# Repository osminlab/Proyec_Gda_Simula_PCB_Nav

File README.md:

<!-- Para mejorar la estructura de mi README.md hice uso de la siguiente web y criterios personales:
    	                https://www.makeareadme.com/
 -->

# **Proyecto de Graduación:** "Simulación de trayectoria de un globo sonda para dimensionamiento de subsistema de navegación para misiones a la estratosfera" 🎈

**ESTADO: Finalizado Junio/2023 (CERRADO).**

El presente es una simulación de trayectoria ascendete y descendete de un globo-sonda hasta los 30 Km en el cual se  analizaron diferentes parámetros que se consideron clave a lo largo de su recorrido, se elaboró un análisis exploratorio (EDA) en los datos generados en la simulación  que finalizó con una propuesta de dimensionamiento a subsistema de navegación Low-cost, desarrollando su respectivo esquemático del circuito y layout de la PCB para una posible fabricación.  

Este es un proyecto de graduación, realizado en la [Universidad Don Bosco (UDB)](https://www.udb.edu.sv/udb/) por Osmin Larreynaga con asesoria de Msc. Napoleón Cornejo. Este microproyecto (trabajo de graduación) forma parte del macroproyecto "Diseño de una misión  globo de gran altitud - StratoBallon" realizado con una dependencia de la universidad llamada [Observatorio Micro Macro (OMM)](http://omm.udb.edu.sv/omm/public/) 

## Indice: 
- [Generalidades del Trabajo](#Generalidades-trabajo)
- [Estructura del repositorio (sub-carpetas)](#estructura-del-repositorio--sub-carpetas)
  * [Carpeta code](#estructura-del-repositorio--sub-carpetas)
  * [Carpeta document](#estructura-del-repositorio--sub-carpetas)
  * [Carpeta hardware](#estructura-del-repositorio--sub-carpetas)
- [Puntos destacados](#puntos-destacados)
- [Licencia](#licencia)

<h2> 
    
    Generalidaddes del Trabajo ⚙️💡
</h2>  

Este repositorio incluye  como producto final lo siguiente:

* **Simulación:** Código fuente escrito en Python de la "Simulacion de trayectoria del Globo de Gran Altitud" haciendo usos de Jupyter Notebooks. [Ver código](https://github.com/osminlab/Proyec_Gda_Simula_PCB_Nav/tree/main/code) o revisar en la sigiente ruta `./code/src`.
* **Documento:**  Escrito final del proyecto de graduación desarrollado en $\LaTeX$, se registra académicamente en detalle y de forma formal en que consiste el presente trabajo. Puede ver el documento en PDF si desconoce sobre $\LaTeX$ click [aquí](https://github.com/osminlab/Proyec_Gda_Simula_PCB_Nav/blob/main/document/TrabajoGraduacion_2023_OsminLarreynaga.pdf) o en la siguietne ruta `./document/TrabajoGraduacion.pdf`.
* **Dimensionamiento subsistema de Navegación:** Se presentan el esquema circuito, layout y vista 3D en Fusion360, además se exportan a Eagle para mayor compatibilidad. [Ver propuesta](https://github.com/osminlab/Proyec_Gda_Simula_PCB_Nav/tree/main/hardware) o revisar en la sigiente ruta `./hardware`.

Todo lo anterior, fue divido en el actual directorio en sub-carpetas. Cada una continene el relativo producto final, revisesé según necesidad de consulta.

<h2> 
    
    Estructura del repositorio (sub-carpetas) 📂🗃️
</h2>  

La estructura del proyecto es la siguiente:

    ├── code            ◄---- Sub-carpeta. Códigos
    ├── document        ◄---- Sub-carpeta. Documentación de trabajo de graduación
    ├── hardware        ◄---- Sub-carpeta. Archivos de placa PCB.
    ├── .gitignore      ◄---- Archivo. Ignora archivos no vitales en el repositorio. 
    ├── LICENSES        ◄---- Sub-carpeta. Licencias del trabajo.
    └── README.md       ◄---- Archivo actual.

A continuación se detalla de forma breve el contenido de cada subcarpeta.

* **Carpeta code**: En el folder  `./code`  se encuentran todo lo relacionado con el simulador  y sus codigos respectivos en Python.

* **Carpeta document**: En `./document` se concentran todos los archivos relativos al documento final del trabajo que cualquier **${\LaTeX}$ editor** puede usar para mostrar el trabajo presente. El archivo principal esta localizado en `document/main_TrabajoGraduacion.tex`, este llama a todo los demás archivos relativos del documento incluyendo tablas, imagenes, capítulos, portada, etc.

    > **NOTA:** [main_TrabajoGraduacion.tex](https://github.com/osminlab/Proyec_Gda_Simula_PCB_Nav/blob/main/document/main_TrabajoGraduacion.tex) es el archivo principal del documento. El PDF final se puede encontrar [Aquí](https://github.com/osminlab/Proyec_Gda_Simula_PCB_Nav/blob/main/document/TrabajoGraduacion_2023_OsminLarreynaga.pdf). Este archivo es el responsable que el compilador de  $\LaTeX$ genere el documento. Sin embargo, para mantenener una código limpio, las secciones principales están localizadas en carpeta [sections](https://github.com/osminlab/Proyec_Gda_Simula_PCB_Nav/tree/main/document/sections).

* **Carpeta hardware**: En el folder  `./hardware`  se encuentran el dimensionamiento de subsistema de navegación. 

<h2> 
    
    Puntos destacados 📝
</h2> 

Son detalles relevantes y generales  en  el trabajo podrían ser: 

* Se logró describir la trayectoria de un globo-sonda temporal y espacialmente, obteniendo gran cantidad de datos sobre parámetros que afecta la simulación. El simulador es preliminar, sin embargo, da buenas ideas del comportamiento de su recorrido.

* Se hizo una aproximación de forma introductoria a un subsistema de navegación para misiones Near-Space.

<h2> 
    
    Licencia ®️
</h2> 

En general se pone a disposición de lo que tome como conveniente de licencia la [Universidad Don Bosco (UDB)](https://www.udb.edu.sv/udb/) en trabajos de este tipo. 
<br>

Sin embargo, de no decir lo anterior se tiene que:
- **Documento:** el documento de este trabajo como lo relativo al documento [`TrabajoGraduacion_2023_OsminLarreynaga.pdf`](https://github.com/osminlab/Proyec_Gda_Simula_PCB_Nav/blob/main/document/TrabajoGraduacion_2023_OsminLarreynaga.pdf) ubicado en carpeta `./document`, todo esta bajo licencia [CC-BY-SA-4.0](https://creativecommons.org/licenses/by-sa/4.0/legalcode). 

- **Hardware:** hablese de dimensionamiento de subsistema de navegación en carpeta `./hardware` bajo licencia [ CERN-OHL-P-2.0](https://ohwr.org/cern_ohl_p_v2.txt).

- **Software:** es decir códigos en python en carpeta `./code` bajo licencia [GNU LGPLv3](https://www.gnu.org/licenses/lgpl-3.0.en.html#license-text).

En carpeta `LICENSES` se tiene un compendio donde se puede leer cada una de las licencias utilizadas en este trabajo.

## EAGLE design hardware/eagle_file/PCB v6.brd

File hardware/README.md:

# Hardware, Subsistema de Navegación ⚙

Se ilustra el dimensionamiento, a continuación: 

<br>

<br>

Si se desea saber lo perteneciendo a esto por favor leer el documento, y el capítulo 4 del trabajo de graduación. Ver PDF del trabajo de graduación [[aquí](https://github.com/osminlab/Proyec_Gda_Simula_PCB_Nav/blob/main/document/TrabajoGraduacion_2023_OsminLarreynaga.pdf)]  o en la presente carpeta en archivo `/document/TrabajoGraduacion.pdf`. 
<br>
<br>

## Detalles Subsistema de Navegación:

Debido a que es un dimensionamiento lo siguiente puede variar, pero se recomienda en carecidamente tenerlas en cuenta:
- Placa de circuito impreso, en los archivos gerber comprimidos, listos para realizar pruebas con los módulos. Si las pruebas son exitosas, puede fabricarse utilizando FR4 estándar para prototipos e Isola FR408HR para vuelo.
- Se utilizaron los siguientes modulos/sensores: como GNSS ([Neo-M9N SparkFun](https://www.sparkfun.com/products/17285)), como registro de vuelo ([Open Log](https://www.sparkfun.com/products/13712)), como sensor barométrico ([MS5611-01BA03](https://www.te.com/commerce/DocumentDelivery/DDEController?Action=showdoc&DocId=Data+Sheet%7FMS5611-01BA03%7FB3%7Fpdf%7FEnglish%7FENG_DS_MS5611-01BA03_B3.pdf%7FCAT-BLPS0036)), como sensor inercial/IMU ([LSM9DS1](https://www.adafruit.com/product/4634)).  Los siguientes pueden ser opcionales: sensor de temperatura (PT1000) y computadora de vuelo (Arduino Nano o STM32 NUCLEO-L432KC).

<br>

## Recomendación

Lo mostrado en este trabajo fue una propuesta en base a la bibliografía consultada, no se realizaron ninguna tipo de pruebas ni de funcionamiento ni de las condiciones atmosféricas. Tomar estra propuesta con el respectivo cuidado y de retomarse hacer las pruebas pertinentes.

Si se desea retomar este trabajo por favor realizar pruebas de funcionamientos con los módulos presentados.

## Licencia 

En carpeta `./hardware` bajo licencia [ CERN-OHL-P-2.0](https://ohwr.org/cern_ohl_p_v2.txt).

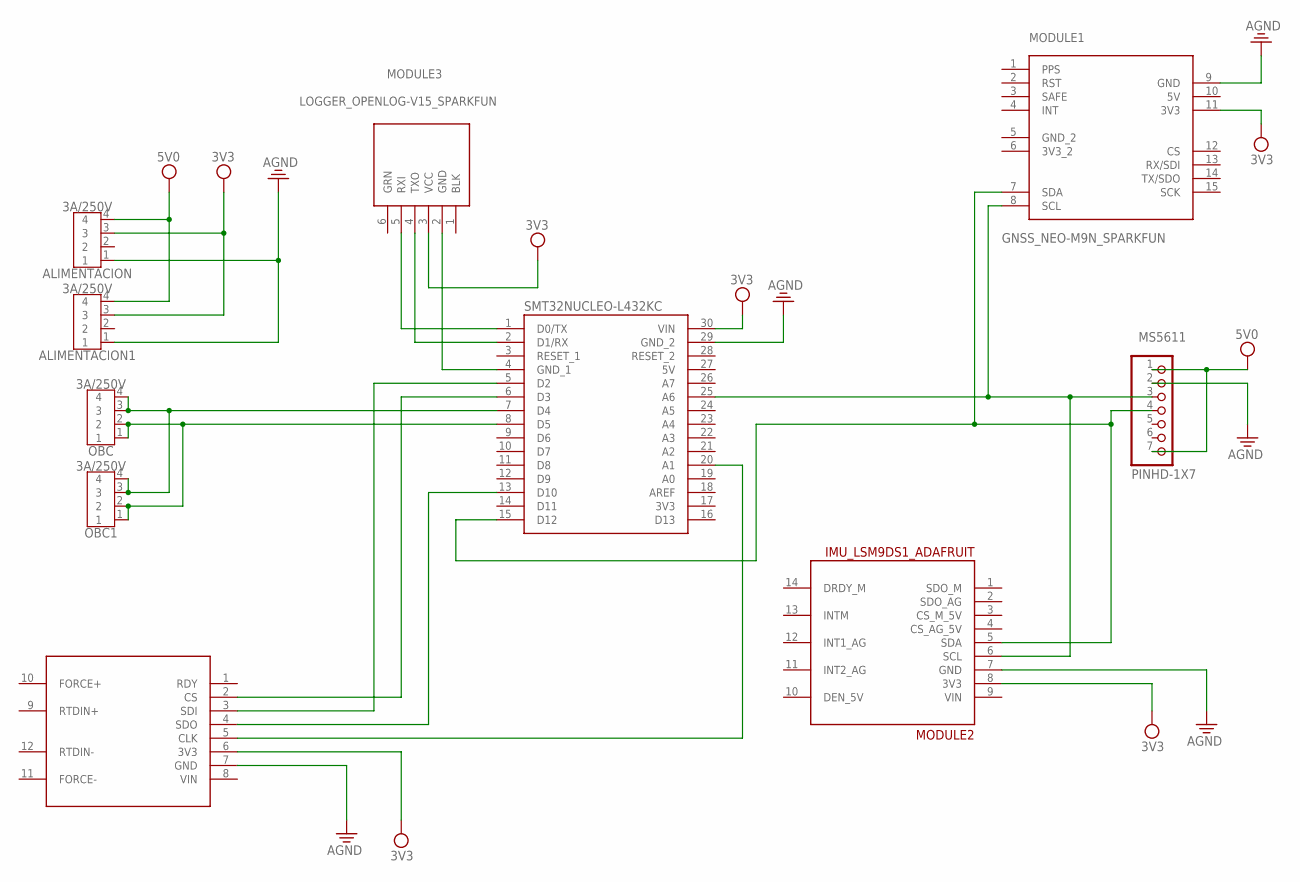
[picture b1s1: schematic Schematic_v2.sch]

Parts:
ALIMENTACION, ALIMENTACION1: 3A/250V; B4B-XH-A
MODULE1: GNSS_NEO-M9N_SPARKFUN; GNSS
MODULE2: IMU_LSM9DS1_ADAFRUIT; IMU
MODULE3: LOGGER_OPENLOG-V15_SPARKFUN; LOGGER
MS5611: PINHD-1X7; 1X07
OBC, OBC1: 3A/250V; B4B-XH-A
PT1000+MAX: TEMP_MAX31865_ADAFRUIT; TEMP
SMT32NUCLEO-L432KC: NANO_ATMEGA328; MODULE_A000005

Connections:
3V3: ALIMENTACION.3, ALIMENTACION1.3, MODULE1.11 (3V3), MODULE2.8 (3V3), MODULE3.3 (VCC), PT1000+MAX.6 (3V3), SMT32NUCLEO-L432KC.17 (3V3)
5V: SMT32NUCLEO-L432KC.27 (5V)
5V0: ALIMENTACION.4, ALIMENTACION1.4, MS5611.1, MS5611.7, SMT32NUCLEO-L432KC.30 (VIN)
AGND: ALIMENTACION.1, ALIMENTACION1.1, MODULE1.9 (GND), MODULE2.7 (GND), MS5611.2, PT1000+MAX.7 (GND), SMT32NUCLEO-L432KC.29 (GND_2)
GND: MODULE3.2 (GND), SMT32NUCLEO-L432KC.4 (GND_1)
unnamed: MODULE1.7 (SDA), MODULE2.5 (SDA), MS5611.4, SMT32NUCLEO-L432KC.15 (D12)
unnamed: PT1000+MAX.5 (CLK), SMT32NUCLEO-L432KC.20 (A1)
unnamed: PT1000+MAX.2 (CS), SMT32NUCLEO-L432KC.6 (D3)
unnamed: MODULE3.5 (RXI), SMT32NUCLEO-L432KC.1 (D0/TX)
unnamed: MODULE3.4 (TXO), SMT32NUCLEO-L432KC.2 (D1/RX)
unnamed: MODULE1.8 (SCL), MODULE2.6 (SCL), MS5611.3, SMT32NUCLEO-L432KC.25 (A6)
unnamed: PT1000+MAX.3 (SDI), SMT32NUCLEO-L432KC.5 (D2)
unnamed: PT1000+MAX.4 (SDO), SMT32NUCLEO-L432KC.13 (D10)
unnamed: OBC.1, OBC.2, OBC1.1, OBC1.2, SMT32NUCLEO-L432KC.8 (D5)
unnamed: OBC.3, OBC.4, OBC1.3, OBC1.4, SMT32NUCLEO-L432KC.7 (D4)

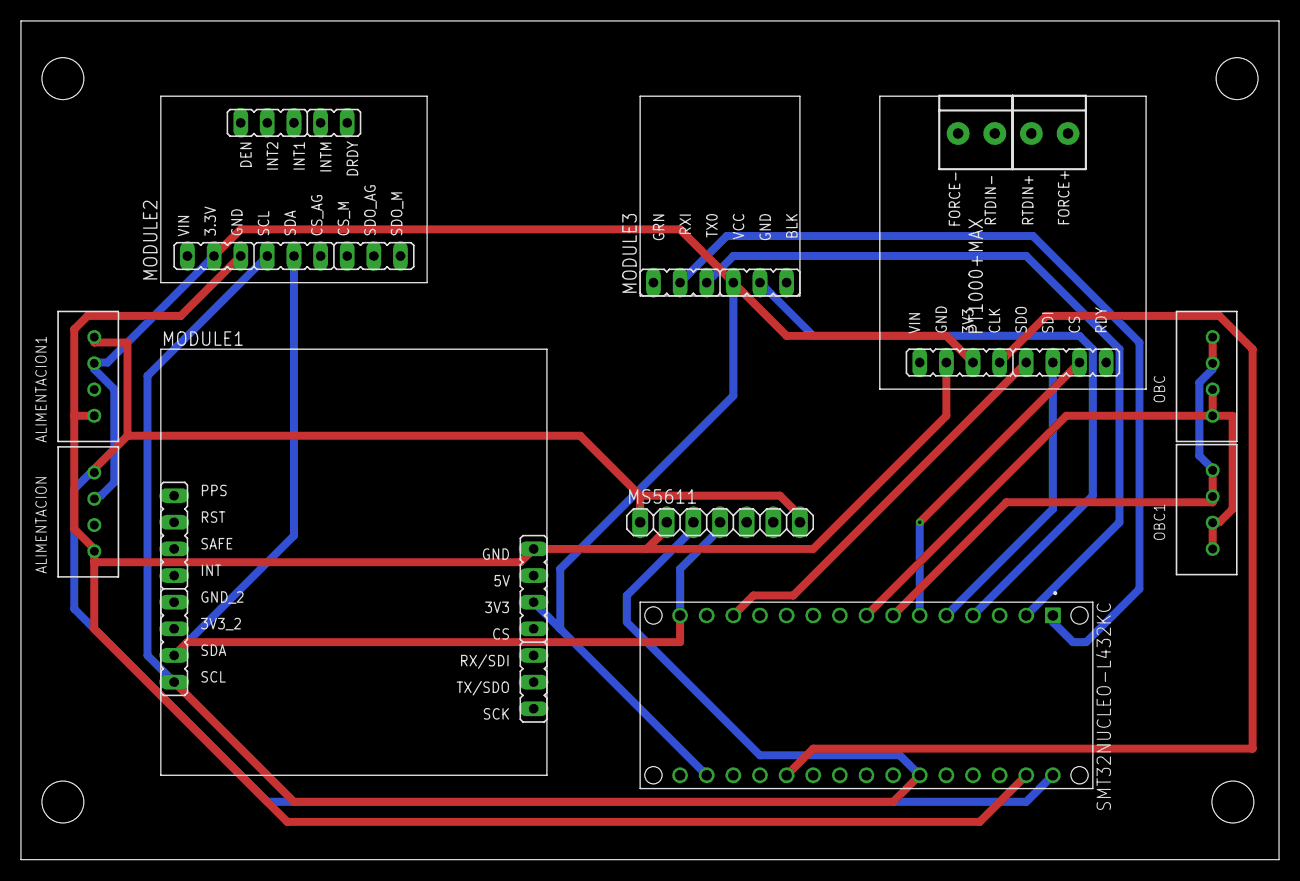
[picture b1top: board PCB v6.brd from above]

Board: 2 copper layers, 120.0 x 80.0 mm, 10 parts (0 on the bottom side), 14 nets.

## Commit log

2024-12-30 Created using Colab
